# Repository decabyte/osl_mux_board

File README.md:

OSL MUX Board
=============

The __OSL MUX board__ is a small standalone 2-layer pcb design for providing I2C multiplexing capabilities to embedded boards (like the Arduino platform) often used in small robotics projects.

This board has been design to be used in motor control problems for a robotic platform using I2C thrusters. This design is using I2C bus extenders to allow operations over longer connections. The following layout ([eagle file](mux_board_final.sch)) is taken as reference where the I2C multiplexer chip of choice is an NXP PCA9547D 8 channel one. This solution can be used with its sister project the __[OSL I2C Buff Board](https://github.com/decabyte/osl_buff_board)__.

The main features are the availability up to 6 multiplexed channels with bus extender output, the presence of TVS protection diodes on the +5V volts and I2C input lines, the address selection jumper headers, the presence of pull-up +5V resistors. The design offers also a reset jumper header and a power-on LED indicator. This solution can be easily modified if the bus extenders are not needed by simply bypassing their connections. If +3.3V or different pull-up voltages are needed the correspondant resistors must be left out and the pull-up function has to be provided externally. This board has been designed together with Arnau Puig Mensa.

### Components

* 1 x NXP PCA9547D I2C multiplexer (8 ch)
* 6 x NXP P82B715PN I2C bus extender
* 3 x SA5.0A 5.0V TVS protection diodes

For a more detailed list look at [the bill of materials](docs/BOM) in the [docs](docs) dir.

## References

* [NXP PCA9547D](http://www.nxp.com/products/interface_and_connectivity/i2c/i2c_multiplexers_switches/series/PCA9547.html)
* [NXP P82B715PN](http://www.nxp.com/products/interface_and_connectivity/i2c/i2c_bus_repeaters_hubs_extenders/P82B715PN.html)
* [Arduino WireLibrary Details](http://playground.arduino.cc/Main/WireLibraryDetailedReference)

## LICENSE - "MIT License"

Copyright (c) 2013-2014 Valerio De Carolis, http://decabyte.it

Permission is hereby granted, free of charge, to any person
obtaining a copy of this software and associated documentation
files (the "Software"), to deal in the Software without
restriction, including without limitation the rights to use,
copy, modify, merge, publish, distribute, sublicense, and/or sell
copies of the Software, and to permit persons to whom the
Software is furnished to do so, subject to the following
conditions:

The above copyright notice and this permission notice shall be
included in all copies or substantial portions of the Software.

THE SOFTWARE IS PROVIDED "AS IS", WITHOUT WARRANTY OF ANY KIND,
EXPRESS OR IMPLIED, INCLUDING BUT NOT LIMITED TO THE WARRANTIES
OF MERCHANTABILITY, FITNESS FOR A PARTICULAR PURPOSE AND
NONINFRINGEMENT. IN NO EVENT SHALL THE AUTHORS OR COPYRIGHT
HOLDERS BE LIABLE FOR ANY CLAIM, DAMAGES OR OTHER LIABILITY,
WHETHER IN AN ACTION OF CONTRACT, TORT OR OTHERWISE, ARISING
FROM, OUT OF OR IN CONNECTION WITH THE SOFTWARE OR THE USE OR
OTHER DEALINGS IN THE SOFTWARE.

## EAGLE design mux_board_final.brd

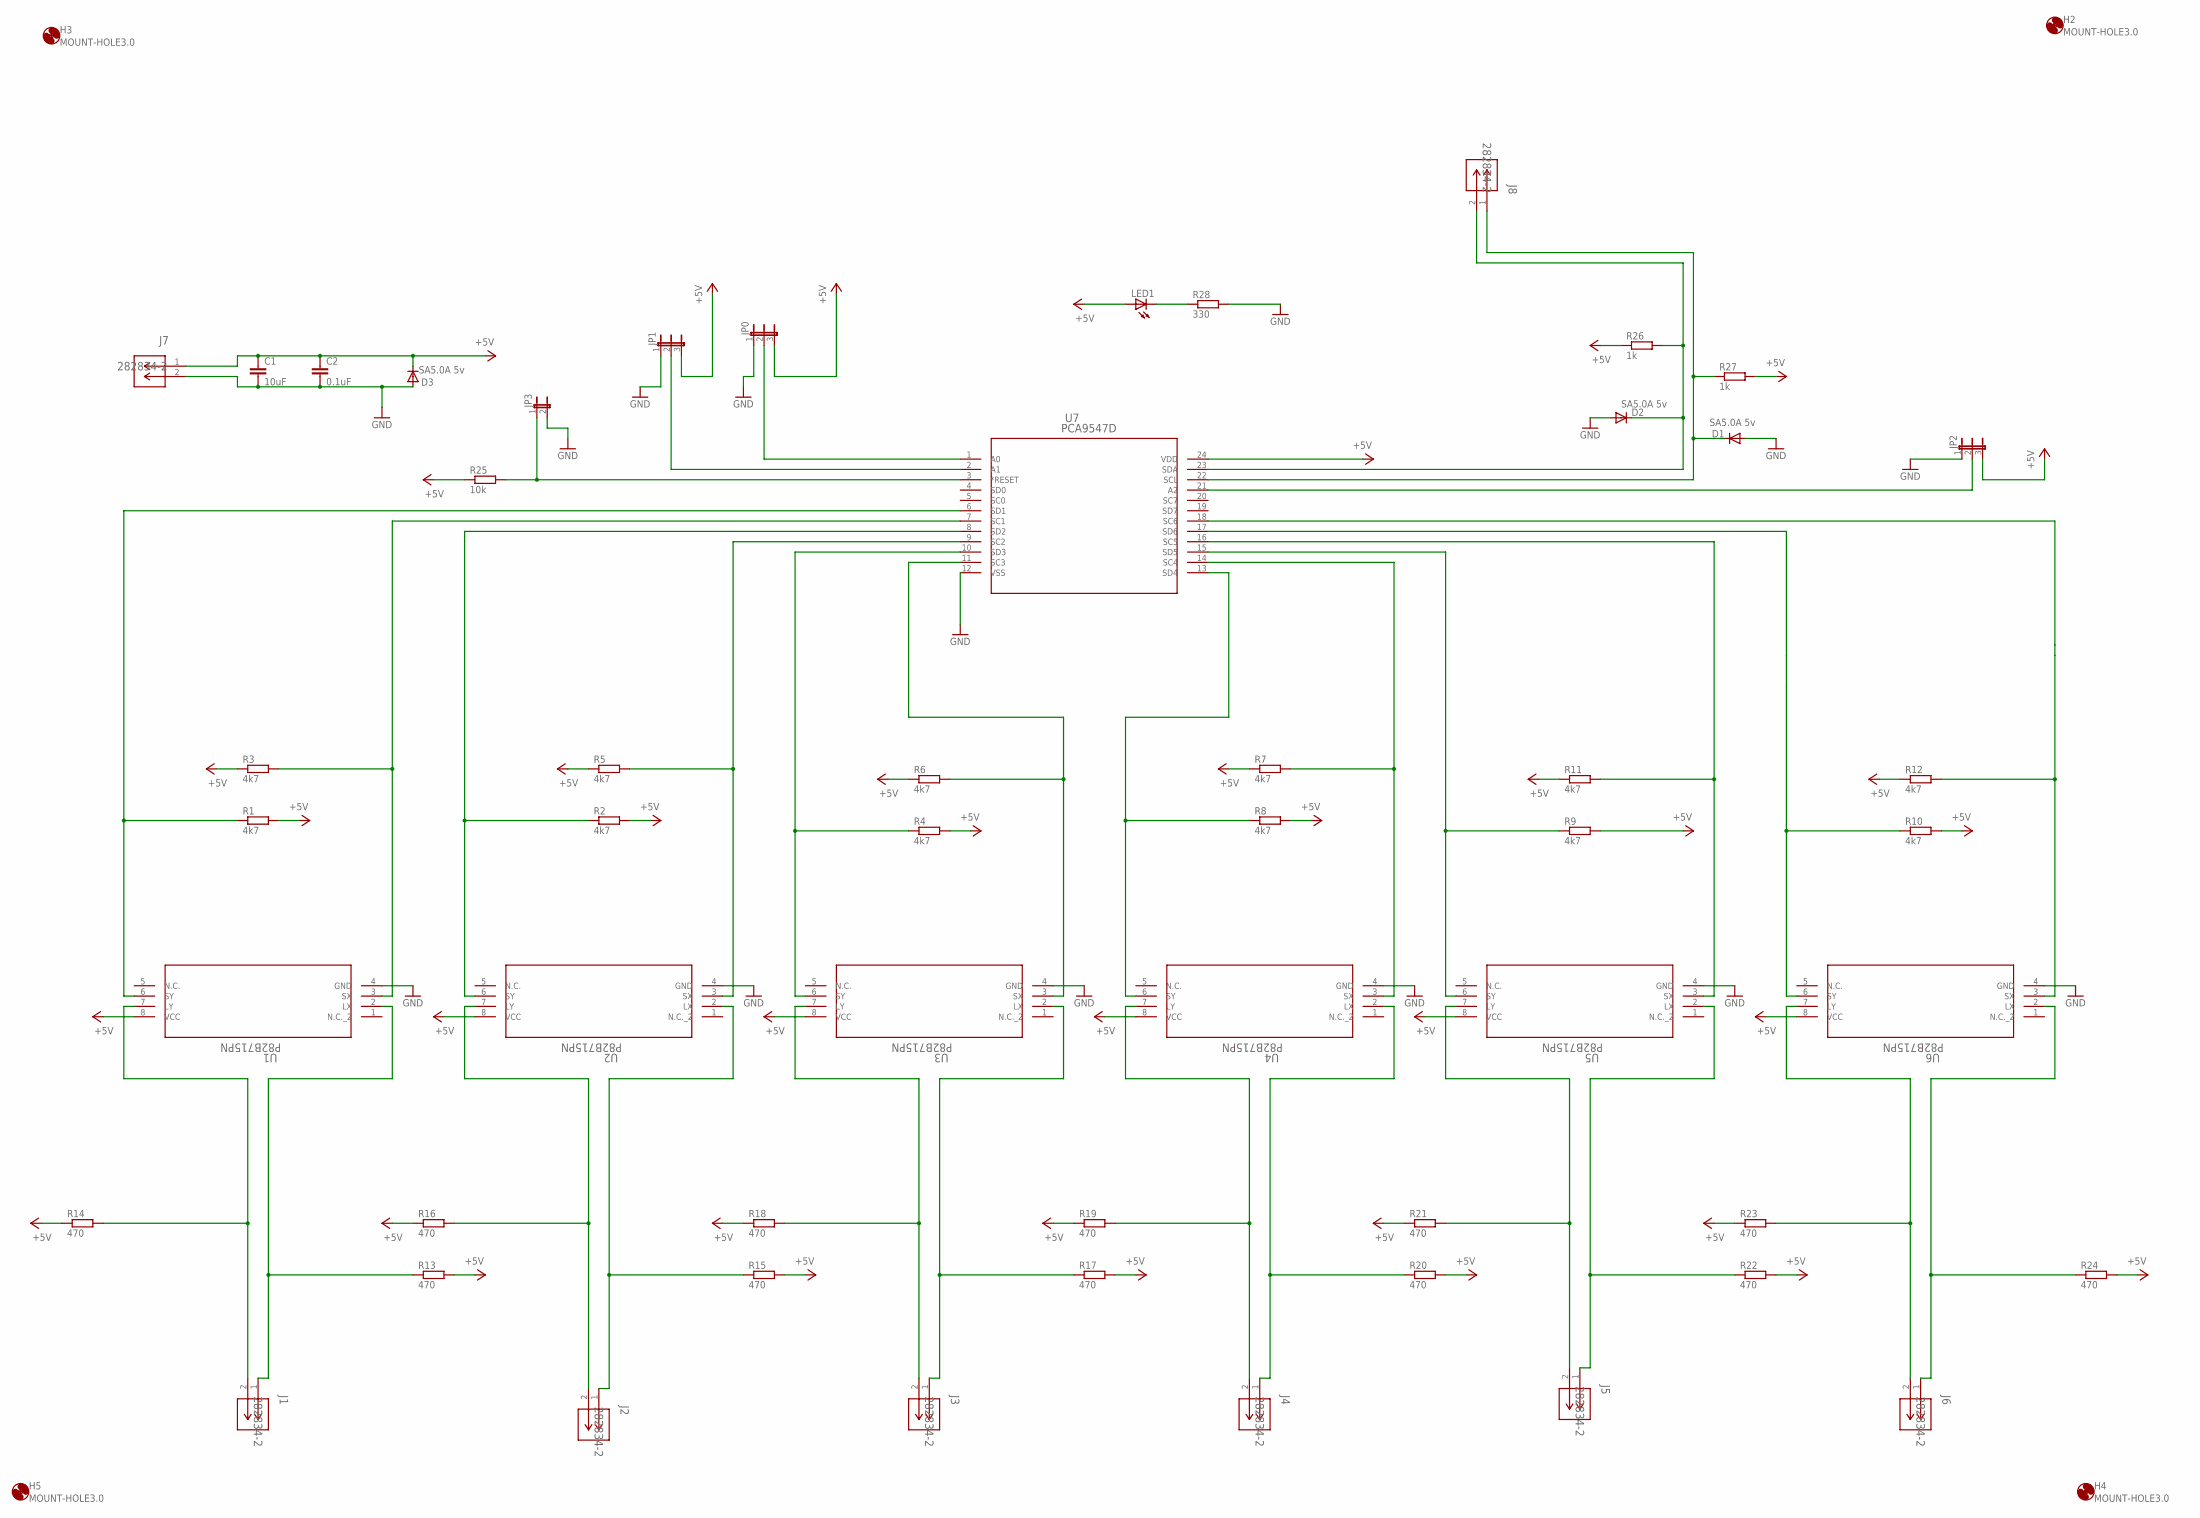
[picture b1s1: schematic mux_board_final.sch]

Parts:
C1: 10uF; C025-025X050
C2: 0.1uF; C025-025X050
D1, D2, D3: SA5.0A 5v; DO41-10
H2, H3, H4, H5: MOUNT-HOLE3.0; 3,0
J1, J2, J3, J4, J5, J6, J7, J8: 282834-2; CONN_282834-2
JP0, JP1, JP2: JP2E; JP2
JP3: JP1E; JP1
LED1: LED3MM
R1, R2, R3, R4, R5, R6, R7, R8, R9, R10, R11, R12: 4k7; 0204/7
R13, R14, R15, R16, R17, R18, R19, R20, R21, R22, R23, R24: 470; 0204/7
R25: 10k; 0204/7
R26, R27: 1k; 0204/7
R28: 330; 0204/7
U1, U2, U3, U4, U5, U6: P82B715PN; SOT97-1
U7: PCA9547D; SOT137-1

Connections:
+5V: C1.1, C2.1, D3.C, J7.1, JP0.3, JP1.3, JP2.3, LED1.A, R1.2, R2.2, R3.1, R4.2, R5.1, R6.1, R7.1, R8.2, R9.2, R10.2, R11.1, R12.1, R13.2, R14.1, R15.2, R16.1, R17.2, R18.1, R19.1, R20.2, R21.1, R22.2, R23.1, R24.2, R25.1, R26.1, R27.2, U1.8 (VCC), U2.8 (VCC), U3.8 (VCC), U4.8 (VCC), U5.8 (VCC), U6.8 (VCC), U7.24 (VDD)
GND: C1.2, C2.2, D1.A, D2.A, D3.A, J7.2, JP0.1, JP1.1, JP2.1, JP3.2, R28.2, U1.4 (GND), U2.4 (GND), U3.4 (GND), U4.4 (GND), U5.4 (GND), U6.4 (GND), U7.12 (VSS)
unnamed: R1.1, U1.6 (SY), U7.6 (SD1)
unnamed: R2.1, U2.6 (SY), U7.8 (SD2)
unnamed: R3.2, U1.3 (SX), U7.7 (SC1)
unnamed: R5.2, U2.3 (SX), U7.9 (SC2)
unnamed: R4.1, U3.6 (SY), U7.10 (SD3)
unnamed: R6.2, U3.3 (SX), U7.11 (SC3)
unnamed: R8.1, U4.6 (SY), U7.13 (SD4)
unnamed: R7.2, U4.3 (SX), U7.14 (SC4)
unnamed: R9.1, U5.6 (SY), U7.15 (SD5)
unnamed: R11.2, U5.3 (SX), U7.16 (SC5)
unnamed: R10.1, U6.6 (SY), U7.17 (SD6)
unnamed: R12.2, U6.3 (SX), U7.18 (SC6)
unnamed: JP0.2, U7.1 (A0)
unnamed: JP1.2, U7.2 (A1)
unnamed: JP2.2, U7.21 (A2)
unnamed: J1.2, R14.2, U1.7 (LY)
unnamed: JP3.1, R25.2, U7.3 (*RESET)
unnamed: J2.2, R16.2, U2.7 (LY)
unnamed: J2.1, R15.1, U2.2 (LX)
unnamed: J3.2, R18.2, U3.7 (LY)
unnamed: J3.1, R17.1, U3.2 (LX)
unnamed: J4.2, R19.2, U4.7 (LY)
unnamed: J4.1, R20.1, U4.2 (LX)
unnamed: J5.2, R21.2, U5.7 (LY)
unnamed: J5.1, R22.1, U5.2 (LX)
unnamed: J6.2, R23.2, U6.7 (LY)
unnamed: J6.1, R24.1, U6.2 (LX)
unnamed: D1.C, J8.1, R27.1, U7.22 (SCL)
unnamed: LED1.K (C), R28.1
unnamed: D2.C, J8.2, R26.2, U7.23 (SDA)
TSR1: J1.1, R13.1, U1.2 (LX)

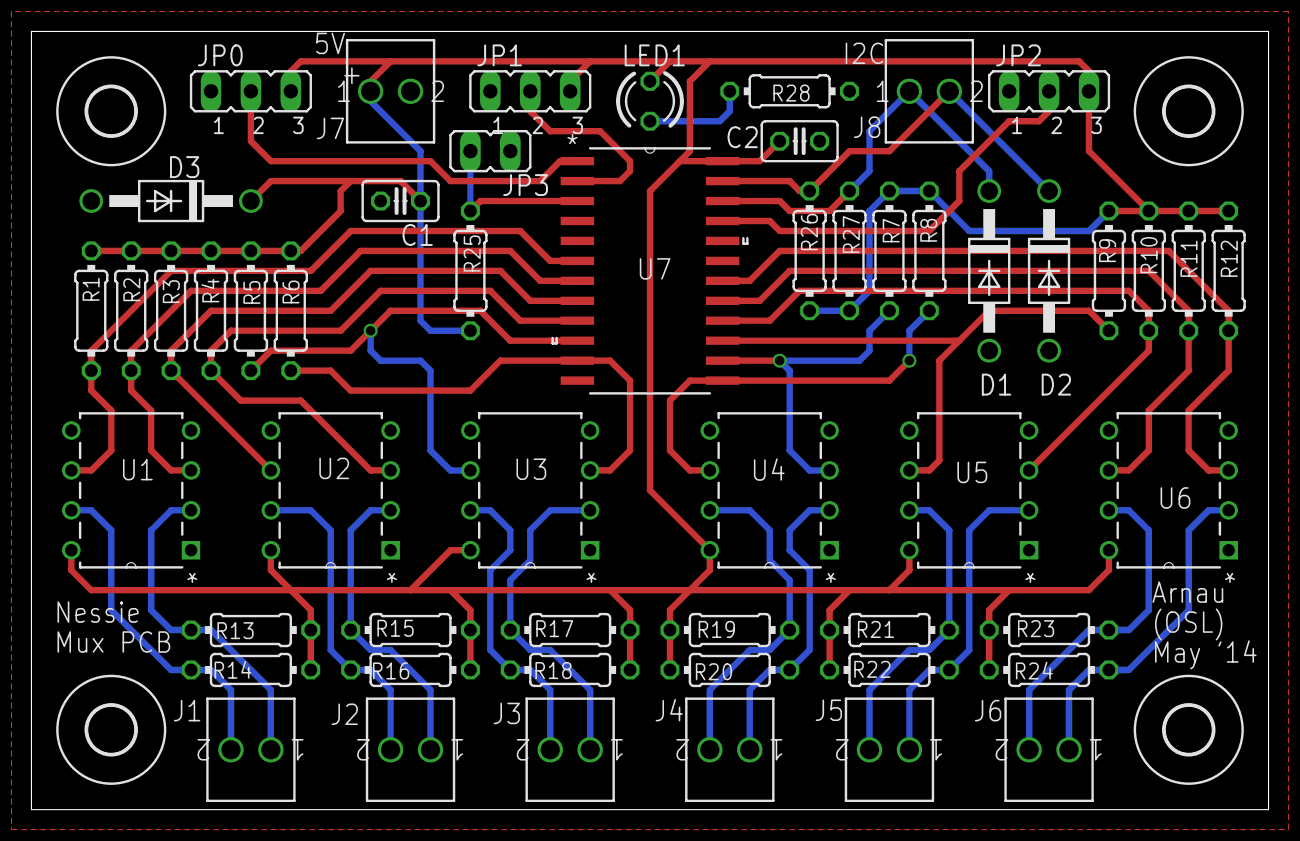
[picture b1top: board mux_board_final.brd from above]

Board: 2 copper layers, 78.7 x 49.5 mm, 57 parts (0 on the bottom side), 33 nets.
